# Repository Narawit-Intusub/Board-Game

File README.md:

# Modular Smart LED Matrix (กระดานไฟ LED อัจฉริยะต่อขยายได้อิสระสำหรับระบบเกมกระดาน)

---

## 1. ภาพรวมโปรเจกต์ (Project Overview)

**Modular Smart LED Matrix** คือ กระดานแสดงผลไฟ LED อัจฉริยะแบบต่อขยายได้อิสระ (Modular Interactive Tabletop Gaming Grid) ออกแบบมาเพื่อเป็นกระดานเล่นเกมแบบ Interactive ร่วมกับเอนจินเกม (เช่น Unity หรือ PC) และหน้าจอแสดงผลกราฟิกแบบปรับเปลี่ยนรูปทรงได้อย่างอิสระ

ระบบถูกออกแบบภายใต้สถาปัตยกรรม **Smart Tile (Distributed Grid Architecture)** โดยแต่ละแผ่นกระดานมีขนาด **$192.0 \times 192.0\text{ mm}$ ($19.2 \times 19.2\text{ cm}$)** แบ่งเป็น **16 ช่องตาราง ($4 \times 4$ Cells ช่องละ $48.0 \times 48.0\text{ mm}$)** แต่ละช่องมีไฟ 4 หลอด (รวม 64 หลอดต่อแผ่น) ขับแสดงผลเฉพาะในบอร์ดตัวเองอย่างอิสระ ไม่ต่อสายไฟ LED เป็นโซ่อนุกรมข้ามบอร์ด

```text
Unity / PC
    │
    │ USB DATA
    ▼
┌───────────────────────────────┐
│ MASTER                        │
│                               │
│ ESP32 Gateway                 │
│    │ Internal UART            │
│    ▼                          │
│ ATtiny1604 Tile Controller    │
│    ├── LED Matrix ของ Master  │
│    └── Magnetic Bus N/E/S     │
└───────────────┬───────────────┘
                │
        VBUS, TX, RX, GND
                │
       ┌────────┴────────┐
       ▼                 ▼
┌─────────────┐   ┌─────────────┐
│ Slave Tile  │   │ Slave Tile  │
│ ATtiny1604  │   │ ATtiny1604  │
└─────────────┘   └─────────────┘
```

---

## 2. โครงสร้างระบบ (System Structure)

ชุดต้นแบบประกอบด้วยกระดานทั้งหมด 4 แผ่น:

| บอร์ด | ตัวควบคุม | หน้าที่หลัก |
| :--- | :--- | :--- |
| **Master (1 แผ่น)** | **ESP32 Wemos D1 Mini + ATtiny1604** | • **ESP32:** เกตเวย์เชื่อม Unity ผ่าน USB, เก็บ Topology ทั้งระบบ, คำนวณ Global Grid, แยก Packet ตาม Tile ID, ตรวจสอบสถานะระบบ<br>• **ATtiny1604:** ควบคุม Tile ของ Master, ขับ 64 LEDs, จัดการ Magnetic Bus N/E/S |
| **Slave 1 (1 แผ่น)** | **ATtiny1604** | ขับ LED 64 ดวงในตัว, รับ-ส่งต่อ Packet, ตรวจจับเพื่อนบ้าน |
| **Slave 2 (1 แผ่น)** | **ATtiny1604** | ขับ LED 64 ดวงในตัว, รับ-ส่งต่อ Packet, ตรวจจับเพื่อนบ้าน |
| **Slave 3 (1 แผ่น)** | **ATtiny1604** | ขับ LED 64 ดวงในตัว, รับ-ส่งต่อ Packet, ตรวจจับเพื่อนบ้าน |

### สรุปรวมอุปกรณ์หลักของระบบ:
* **ESP32:** จำนวน 1 ตัว (อยู่บนบอร์ด Master เท่านั้น ทำหน้าที่ Gateway ระดับระบบ)
* **ATtiny1604:** จำนวน 4 ตัว (ประจำทุกแผ่น แผ่นละ 1 ตัว ทำหน้าที่ Tile Controller มาตรฐานเดียวกัน)
* **USB Data:** ต่อคอมพิวเตอร์เฉพาะบอร์ด Master เพียงจุดเดียว
* **Power Input:** จ่ายไฟเข้าที่บอร์ด Master เพียงจุดเดียว แล้วส่งผ่านบัส `VBUS` ไปยังแต่ละแผ่น

---

## 3. หน้าที่ของแต่ละตัวควบคุม

### 3.1 หน้าที่ของ ESP32 (System Gateway)
* ติดต่อกับ Unity ผ่านสาย USB เพียงเส้นเดียว
* รับสถานะเกม ข้อมูลสีพิกัด และคำสั่งเฟรมภาพ
* บันทึกและวิเคราะห์โครงสร้างแผนผังทั้งหมดของระบบ (System Topology)
* คำนวณตำแหน่งสัมพัทธ์และการหมุนของแต่ละ Tile รวมเป็น Global Grid ผืนเดียว
* แยกข้อมูล Packet ตาม Tile ID
* ตรวจสอบสถานะและรายงานความผิดปกติของระบบ
* **ส่ง Packet ทั้งหมดให้ ATtiny1604 ของ Master ผ่าน Internal UART**
* *ESP32 ไม่ต้องต่อเข้าหัวแม่เหล็กภายนอกโดยตรง และไม่ต้องขับ LED โดยตรง*

### 3.2 หน้าที่ของ ATtiny1604 (Tile Controller ประจำทุกแผ่น รวม 4 ตัว)
* มีรหัส **Tile ID** ประจำตัว
* ขับไฟ LED ภายในแผ่นตัวเอง (64 LEDs จากข้อมูลสี 16 ช่อง)
* จัดการหน่วยความจำสี 16 ช่อง (Active Buffer และ Back Buffer)
* รับและส่งต่อ Packet ข้อมูลตามเส้นทางเครือข่าย
* ส่งข้อความ `HELLO` เพื่อค้นหาเพื่อนบ้าน
* **ตรวจจับเพื่อนบ้านและทิศทางการเชื่อมต่อเมื่อได้รับข้อความ `HELLO` ทางขา RX แยกแต่ละทิศ (`LINK_RX_N/E/S/W`)**
* รอรับสัญญาณแสดงผลพร้อมกัน (`FRAME_COMMIT`)
* รายงานสถานะกลับไปยัง ESP32 ผ่านโครงข่ายบัส
* **ATtiny บน Master และ Slave ใช้ Firmware สถาปัตยกรรมพื้นฐานชุดเดียวกัน**

---

## 4. บัสแม่เหล็ก 4 จุด (4-Pin Magnetic Link)

แต่ละขอบที่เชื่อมต่อระหว่างบอร์ดมีพินสัญญาณ 4 พิน:

$$\text{[ VBUS ]} \quad \vert \quad \text{[ LINK_TX ]} \quad \vert \quad \text{[ LINK_RX ]} \quad \vert \quad \text{[ GND ]}$$

```text
  Female Connector (North / East)       Male Connector (South / West)
      +---------------------+               +---------------------+
      | (1)  (2)  (3)  (4)  |               | (1)  (2)  (3)  (4)  |
      | VBUS LinkTX LinkRX GND|             | GND LinkTX LinkRX VBUS|
      +---------------------+               +---------------------+
```

### 4.1 การจับคู่เมื่อประกบบอร์ด (Poka-Yoke 180° Inversion):
เมื่อนำขอบ Female ประกบกับขอบ Male หลังหมุน 180° พินจะจับคู่ตรงกันอย่างถูกต้อง:
* $\text{Pin 1 (VBUS)} \longleftrightarrow \text{Pin 4 (VBUS)}$: บัสไฟเลี้ยงหลัก
* $\text{Pin 2 (LINK_TX)} \longleftrightarrow \text{Pin 3 (LINK_RX)}$: สายส่งข้อมูลชนสายรับข้อมูล
* $\text{Pin 3 (LINK_RX)} \longleftrightarrow \text{Pin 2 (LINK_TX)}$: สายรับข้อมูลชนสายส่งข้อมูล
* $\text{Pin 4 (GND)} \longleftrightarrow \text{Pin 1 (GND)}$: ระนาบกราวด์ร่วม

### 4.2 ทิศทางขั้วต่อในแต่ละบอร์ด:
* **Master มี 3 ทิศ:** **North, East, South** (เว้นด้าน **West** ไว้สำหรับช่องรับไฟหลักและพอร์ต USB สื่อสารกับคอมพิวเตอร์)
* **Slave มีครบ 4 ทิศ:** **North, East, South, West**

### 4.3 สถาปัตยกรรมการรับ-ส่งสัญญาณ (Directional RX & Shared TX):
บนแต่ละ Tile:
* มีขา **LINK_RX แยกอิสระ 4 ทิศทาง:** `LINK_RX_N`, `LINK_RX_E`, `LINK_RX_S`, `LINK_RX_W` ทำให้ระบุทิศทางของแพ็กเก็ตที่ส่งเข้ามาได้อย่างแม่นยำ
* มีขา **LINK_TX หนึ่งเส้นใช้ร่วมกันทุกด้าน:** เมื่อ Tile สั่งส่งข้อมูล ข้อมูลจะบรอดคาสต์ออกไปยังเพื่อนบ้านทุกด้านพร้อมกัน

---

## 5. รูปแบบแพ็กเก็ตและการป้องกันข้อมูลวนซ้ำ (Packet Architecture & Loop Prevention)

เนื่องจากขา `LINK_TX` เป็นสายร่วมที่กระจายสัญญาณออกทุกด้านพร้อมกัน Packet จึงต้องมีโครงสร้างข้อมูลกำกับ:

```text
+-----------+----------------+-----------------+--------------+-----+-----+--------+
| Source ID | Destination ID | Sequence Number | Frame Number | TTL | CRC | Data.. |
+-----------+----------------+-----------------+--------------+-----+-----+--------+
```

* **Source ID / Destination ID:** ระบุโหนดต้นทางและปลายทาง (หรือ Broadcast ID)
* **Sequence Number:** ลำดับของแพ็กเก็ต
* **Frame Number:** เลขเฟรมภาพสำหรับการซิงก์แสดงผล
* **TTL (Time-To-Live):** ลดค่าลงทีละ 1 ทุกครั้งที่ส่งต่อ เพื่อตัดวงจรแพ็กเก็ตตกค้าง
* **CRC:** ตรวจสอบความถูกต้องของข้อมูล
* **การป้องกันข้อมูลวนซ้ำ (Deduplication):** แต่ละ Tile จะจดจำ Sequence Number ล่าสุด และ**ไม่ประมวลผลแพ็กเก็ตเดิมซ้ำ** ช่วยป้องกันปัญหาข้อมูลวนลูปในกรณีที่มีเส้นทางเชื่อมต่อหลายทาง

---

## 6. เส้นทางข้อมูลที่ถูกต้อง (Data Flow Pipeline)

```text
Unity
  └──► ESP32 (Master)
         └──► ATtiny1604 (Master)
                ├──► ขับไฟ LED 64 ดวงบน Master
                └──► Magnetic Link (LINK_TX)
                       └──► ATtiny1604 (Slave Tile)
                              ├──► ขับไฟ LED 64 ดวงบน Slave
                              └──► ส่งต่อไปยัง Slave ถัดไป
```

* **Master Tile:** Unity $\rightarrow$ ESP32 $\rightarrow$ ATtiny Master $\rightarrow$ LED Master
* **Slave Tiles:** Unity $\rightarrow$ ESP32 $\rightarrow$ ATtiny Master $\rightarrow$ Magnetic Link $\rightarrow$ ATtiny Slave $\rightarrow$ ส่งต่อไปยัง Slave ถัดไป
* **ESP32 ไม่ส่งข้าม ATtiny Master ไปยังบอร์ดลูกโดยตรง**

---

## 7. สถาปัตยกรรมระบบไฟ (Power Architecture)

หลักการจ่ายไฟของระบบกำหนดไว้ดังนี้:

```text
Power Input
   └──► Master Protection
          └──► VBUS (ส่งผ่านขั้วต่อแม่เหล็กไปยังทุกแผ่น)
                 └──► Local Power Converter ในแต่ละ Tile
                        └──► 5V คงที่สำหรับขับ LED และเลี้ยง ATtiny1604
```

> [!IMPORTANT]
> **ข้อกำหนดในการออกแบบภาคจ่ายไฟ:**
> 1. **ใช้ชื่อบัสกลางว่า `VBUS`:** ไม่ส่งตรง 5V ผ่านทุกบอร์ดในระยะยาว เพื่อรองรับการจ่ายแรงดันที่สูงขึ้น (เช่น 9V–12V) แล้วใช้ Local Step-Down Converter ลดเป็น 5V ภายในแต่ละแผ่น เพื่อลดแรงดันตกคร่อม (Voltage Drop) และลดกระแสบนพินแม่เหล็ก
> 2. **ยังไม่ล็อกเบอร์อุปกรณ์และแรงดัน VBUS ในสเปกหลัก:** รายละเอียดของแรงดัน VBUS, ชนิดคอนเนคเตอร์ไฟเข้า, ชนิดวงจรแปลงไฟ, อุปกรณ์วัดกระแส, และพิกัด TVS (ห้ามล็อก SMAJ5.0A หาก VBUS มีโอกาสสูงกว่า 5V) จะสรุปหลังจากการทดสอบพิกัดกระแสจริงของหัวแม่เหล็กและกำลังวัตต์สูงสุดของ LED ทั้งระบบ
> 3. **ตัวต้านทาน CC 5.1kΩ:** ทำหน้าที่ระบุสถานะ Sink บนพอร์ต USB Type-C พื้นฐานเท่านั้น ไม่ได้รับรองการจ่ายกระแส 5V/3A และไม่ใช่ระบบเจรจาแรงดัน USB-PD

---

## 8. การจัดการระดับแรงดันสัญญาณ (Logic Level Translation)

* **หาก ATtiny1604 เลี้ยงด้วยไฟ 5V:** สัญญาณ GPIO เอาต์พุต (รวมถึงขาขับ LED `LED_DATA`) จะมีระดับแรงดันเป็น 5V CMOS Logic อยู่แล้ว จึงสามารถขับขา DIN ของโมดูล WS2812B ได้โดยตรงโดยไม่ต้องใช้ Level Shifter 3.3V$\rightarrow$5V หน้า LED
* **จุดที่ต้องแปลงระดับแรงดัน (Level Shifting):** คือส่วนเชื่อมต่อระหว่าง **ESP32 (แรงดันสัญญาณ 3.3V)** กับ **ATtiny1604 (แรงดันสัญญาณ 5V)** บนบอร์ด Master เพื่อให้การส่งข้อมูล UART ภายในทำงานได้อย่างถูกต้องและปลอดภัย

---

## 9. เอกสารอ้างอิงเฉพาะบอร์ด (Detailed Documentation Links)

* 📖 **[เอกสารวงจรและฮาร์ดแวร์บอร์ดแม่ (Master Controller Board README)](hardware/master/README.md)**
* 📖 **[เอกสารวงจรและฮาร์ดแวร์บอร์ดลูก (Slave Expansion Board README)](hardware/slave/README.md)**

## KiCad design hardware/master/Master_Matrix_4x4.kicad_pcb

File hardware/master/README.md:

# Master Controller Board (บอร์ดแม่) - Dual-MCU Smart Tile (ESP32 + ATtiny1604)

เอกสารนี้อธิบายรายละเอียดการออกแบบทางฮาร์ดแวร์ บล็อกการทำงาน หน้าที่ของแต่ละโมดูล และโครงสร้างทางวิศวกรรมของ **Master Controller Board** (ไฟล์ KiCad: [Master_Matrix_4x4.kicad_sch](Master_Matrix_4x4.kicad_sch), [Master_Matrix_4x4.kicad_pcb](Master_Matrix_4x4.kicad_pcb)) ภายใต้สถาปัตยกรรม **Dual-MCU Smart Tile Grid**

---

## 1. ภาพรวมบอร์ดแม่ (Master Board Overview)

**Master Controller Board** ขนาดแผ่น **$192.0 \times 192.0\text{ mm}$ ($19.2 \times 19.2\text{ cm}$)** แบ่งเป็น **16 ช่องตาราง ($4 \times 4$ Cells ช่องละ $48.0 \times 48.0\text{ mm}$)** แต่ละช่องติดตั้งไฟ LED 4 ดวงแบบ $2 \times 2$ (รวม 64 หลอด) ทำหน้าที่เป็นทั้ง **พื้นที่เล่นในตัว** และ **เกตเวย์เชื่อมต่อกับคอมพิวเตอร์/Unity**

### สถาปัตยกรรมชิปคู่บนบอร์ดแม่ (Dual-MCU Architecture):
บอร์ดแม่รวมไมโครคอนโทรลเลอร์ 2 ตัวไว้บนแผ่นเดียว เพื่อแยกบทบาทหน้าที่อย่างชัดเจน:

1. **ESP32 Gateway (`U1`):**
   - เชื่อมต่อกับ Unity / PC ผ่านสาย USB ทางขอบด้านซ้าย (West)
   - รับข้อมูลเกม, สถานะ, ข้อมูลสี และค่าความสว่างจาก Unity
   - เก็บโครงสร้างแผนผังความสัมพันธ์ทั้งระบบ (System Topology Map)
   - คำนวณ Global Grid และแปลงพิกัดสากล
   - แยกข้อมูล Packet ตาม Tile ID
   - ตรวจสอบสถานะการทำงานของระบบ
   - **ส่งทุก Packet ให้ ATtiny1604 ของบอร์ดแม่ผ่าน Internal UART**
   - *ESP32 ไม่ต่อเข้าหัวแม่เหล็กภายนอกโดยตรง และไม่ขับ LED โดยตรง*

2. **ATtiny1604 Master Tile Controller (`U_ATTINY`):**
   - ทำหน้าที่เป็น Smart Tile ประจำบอร์ดแม่ โดยใช้ **Firmware สถาปัตยกรรมเดียวกับบอร์ดลูก**
   - รับ Packet ข้อมูลจาก ESP32
   - จัดการเก็บสี 16 ช่องในหน่วยความจำ (Active Buffer และ Back Buffer)
   - ขับไฟ LED 64 ดวงในบอร์ดตัวเอง (1 สี ขยายออกเป็น 4 หลอดต่อช่อง)
   - ขับสัญญาณออกสู่โครงข่ายแม่เหล็ก 3 ทิศทาง (**North, East, South**) ผ่านสาย `LINK_TX`
   - กระจายสัญญาณและส่งต่อแพ็กเก็ตไปยังบอร์ดลูก

```text
Unity Game Engine
       │ USB DATA
       ▼
+-------------------------------------------------------------------------+
|                        Master Controller Board                          |
|                                                                         |
|                     [ J_NORTH (Female Mag-4P) ]                         |
|                     (VBUS, Link TX, Link RX, GND)                       |
|                                  ^                                      |
|                                  |                                      |
|  [ POWER INPUT ]            +----+----+                                 |
|  [ USB TO UNITY ]           | ATtiny  | <---> [ J_EAST (Female) ]       |
|         │                   |  1604   |       (VBUS, TX, RX, GND)       |
|         ▼                   | Master  |                                 |
|   +-----------+  Internal   +----+----+                                 |
|   |   ESP32   |  UART            | DIN_LOCAL (5V Logic)                 |
|   |  Gateway  | ---------->      v                                      |
|   +-----------+ (Level Shift)+---------------+                          |
|         │                    |  LED Matrix   | (MOD1 -> MOD2 -> .. MOD16|
|  (System Mgmt)               |  (64 LEDs)    | (Local Driving Only)     |
|   (West Edge)                +---------------+                          |
|                                  |                                      |
|                                  v                                      |
|                     [ J_SOUTH (Male Mag-4P) ]                           |
|                     (VBUS, Link TX, Link RX, GND)                       |
+-------------------------------------------------------------------------+
```

---

## 2. ขั้วต่อแม่เหล็ก 3 ทิศทาง (3-Edge Magnetic Link Bus)

บอร์ด Master ติดตั้งขั้วต่อแม่เหล็กที่ขอบบอร์ด **3 ด้านเท่านั้น** ได้แก่ **North, East, South** (เว้นด้าน **West** ไว้สำหรับช่องรับไฟหลักและพอร์ต USB เชื่อมต่อคอมพิวเตอร์):

$$\text{Pin 1: [ VBUS ]} \quad \vert \quad \text{Pin 2: [ LINK_TX ]} \quad \vert \quad \text{Pin 3: [ LINK_RX ]} \quad \vert \quad \text{Pin 4: [ GND ]}$$

```text
  Female Connector (North / East)       Male Connector (South)
      +---------------------+               +---------------------+
      | (1)  (2)  (3)  (4)  |               | (1)  (2)  (3)  (4)  |
      | VBUS LinkTX LinkRX GND|             | GND LinkTX LinkRX VBUS|
      +---------------------+               +---------------------+
```

### การจับคู่สัญญาณเมื่อประกบกัน (Poka-Yoke 180° Inversion):
* **Pin 1 (VBUS) $\longleftrightarrow$ Pin 4 (VBUS):** บัสจ่ายไฟเลี้ยงหลักของโครงข่าย
* **Pin 2 (LINK_TX) $\longleftrightarrow$ Pin 3 (LINK_RX):** สายส่งข้อมูลชนสายรับข้อมูลของเพื่อนบ้าน
* **Pin 3 (LINK_RX) $\longleftrightarrow$ Pin 2 (LINK_TX):** สายรับข้อมูลชนสายส่งข้อมูลของเพื่อนบ้าน
* **Pin 4 (GND) $\longleftrightarrow$ Pin 1 (GND):** ระนาบกราวด์ร่วมของทั้งระบบ

---

## 3. เส้นทางข้อมูลและการกระจายสัญญาณ (Data Routing & Level Shifting)

1. **เส้นทางข้อมูล:**
   * Unity $\rightarrow$ ESP32 (ถอดรหัสและแยก Packet)
   * ESP32 $\rightarrow$ ATtiny Master (ผ่าน Internal UART)
   * ATtiny Master $\rightarrow$ ขับไฟ LED 64 ดวงบนบอร์ด Master
   * ATtiny Master $\rightarrow$ กระจายข้อมูลออกสู่ `LINK_TX` ขั้วต่อแม่เหล็ก N/E/S ไปยังบอร์ดลูก
2. **การแปลงระดับแรงดัน (Level Shifting):**
   * หาก ATtiny1604 ทำงานที่แรงดัน 5V เอาต์พุต GPIO ของ ATtiny จะเป็น 5V Logic อยู่แล้ว จึงขับขา DIN ของ WS2812B ได้โดยตรง
   * จุดที่ต้องแปลงระดับแรงดันคือระหว่าง **ESP32 (3.3V Logic)** กับ **ATtiny1604 (5V Logic)** บนสัญญาณ UART ภายใน เพื่อความเข้ากันได้ทางไฟฟ้าและความปลอดภัยของชิป
   * ทิศ ESP32 → ATtiny ใช้ `74AHCT1G125`; ทิศ ATtiny → ESP32 ใช้ตัวแบ่งแรงดัน 10kΩ/20kΩ เพื่อจำกัดสัญญาณประมาณ 3.3V
3. **Current monitor:** บัส I²C ของ INA219 มี pull-up 4.7kΩ ไปยัง `+3V3` แยกทั้ง SDA และ SCL

---

## 4. สถาปัตยกรรมระบบไฟ (Power Architecture)

หลักการจ่ายไฟของระบบ:
```text
Power Input
   └──► Master Protection
          └──► VBUS ผ่านขั้วต่อแม่เหล็ก
                 └──► Local Power Converter ในแต่ละ Tile
                        └──► 5V คงที่สำหรับขับ LED และเลี้ยง ATtiny1604
```

> [!NOTE]
> **การกำหนดสเปกภาคจ่ายไฟ:**
> * บัสส่งไฟระหว่างบอร์ดใช้ชื่อกลางว่า **`VBUS`** เพื่อรองรับการทดสอบแรงดันที่เหมาะสม (เช่น 5V ตรง หรือ 9V–12V ร่วมกับ Local Step-Down Converter) เพื่อลดปัญหากระแสสูงและแรงดันตกคร่อมบนพินแม่เหล็ก
> * สเปกของ Power Input, พิกัดแรงดัน VBUS, วงจรตรวจวัดกระแส, และเบอร์ไดโอด TVS จะถูกกำหนดอย่างเป็นทางการหลังทราบพิกัดกระแสจริงของหัวแม่เหล็กและกำลังวัตต์สูงสุดของ LED ทั้งระบบ (ไม่ล็อกเบอร์ SMAJ5.0A หาก VBUS ถูกปรับขึ้นสูงกว่า 5V)
> * ตัวต้านทาน CC 5.1kΩ บนพอร์ต Type-C ทำหน้าที่ระบุสถานะ Sink พื้นฐาน ไม่ได้รับรองการจ่าย 5V/3A และไม่ใช่ระบบ USB-PD
> * `R_BUS` เป็น **DNP โดยปริยาย** ห้ามประกอบเป็น 0Ω จนกว่าจะยืนยันว่าใช้ VBUS 5V แบบจำกัดกระแส หากต้องการขยายหลาย Tile ให้แทนตำแหน่งนี้ด้วย Local Power Converter ที่เลือกตามพิกัดจริง
> * ขา `VCC_(USB)` ของโมดูล ESP32 ไม่ผูกเข้ากับราง `+5V` ภายนอก เพื่อป้องกันการป้อนไฟย้อนเข้าสาย USB Data ของคอมพิวเตอร์

---

## 5. การส่งแพ็กเก็ตและตรวจจับเพื่อนบ้าน

* **การส่งข้อมูล (`LINK_TX`):** ATtiny Master ส่งออกทาง `LINK_TX` ซึ่งเชื่อมขนานไปยังขั้วต่อ N, E, S สัญญาณจะออกไปยังเพื่อนบ้านทุกด้านพร้อมกัน
* **การป้องกันข้อมูลวนซ้ำ (Deduplication):** Packet จะระบุ `Source ID`, `Destination ID`, `Sequence Number`, `Frame Number`, `TTL`, และ `CRC` ทุกโหนดจะไม่ประมวลผล Packet เดิมซ้ำ
* **การค้นหาเพื่อนบ้าน (Neighbor Discovery):** ขา `LINK_RX` แยกตามทิศทาง (`LINK_RX_N`, `LINK_RX_E`, `LINK_RX_S`) เมื่อได้รับข้อความ `HELLO` ทางขาใด จะทำให้ ATtiny ทราบทิศทางและบอร์ดที่เชื่อมต่ออยู่ทันที และส่งรายงานกลับไปยัง ESP32

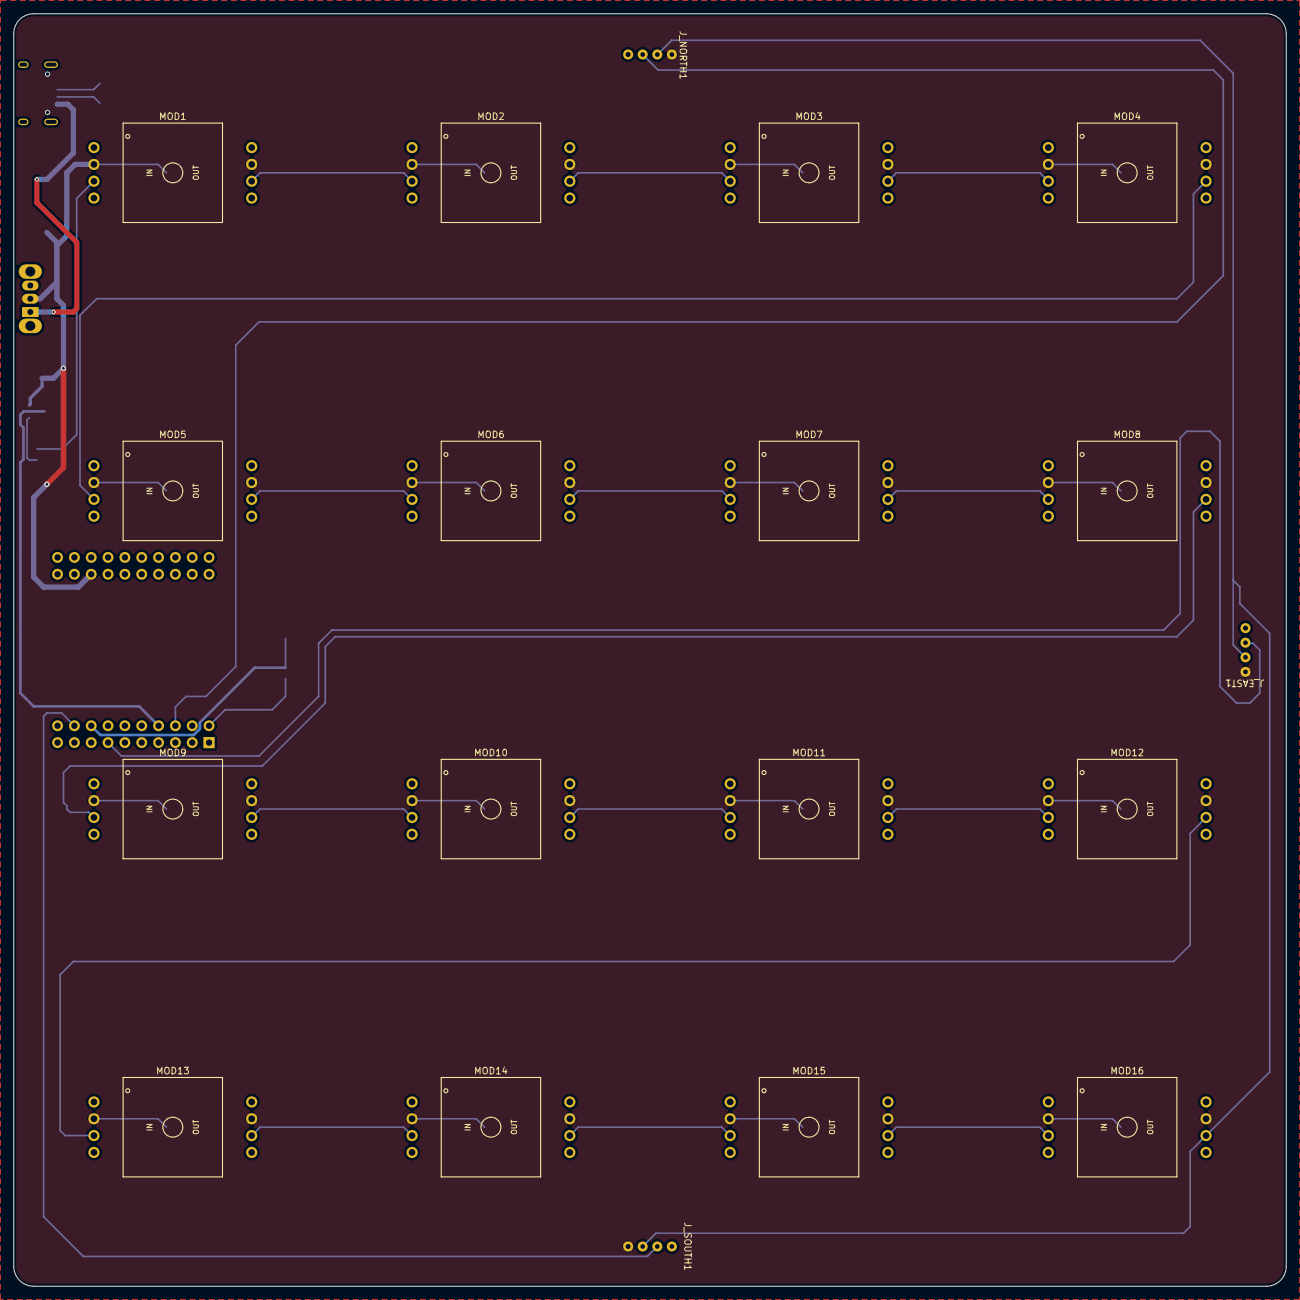
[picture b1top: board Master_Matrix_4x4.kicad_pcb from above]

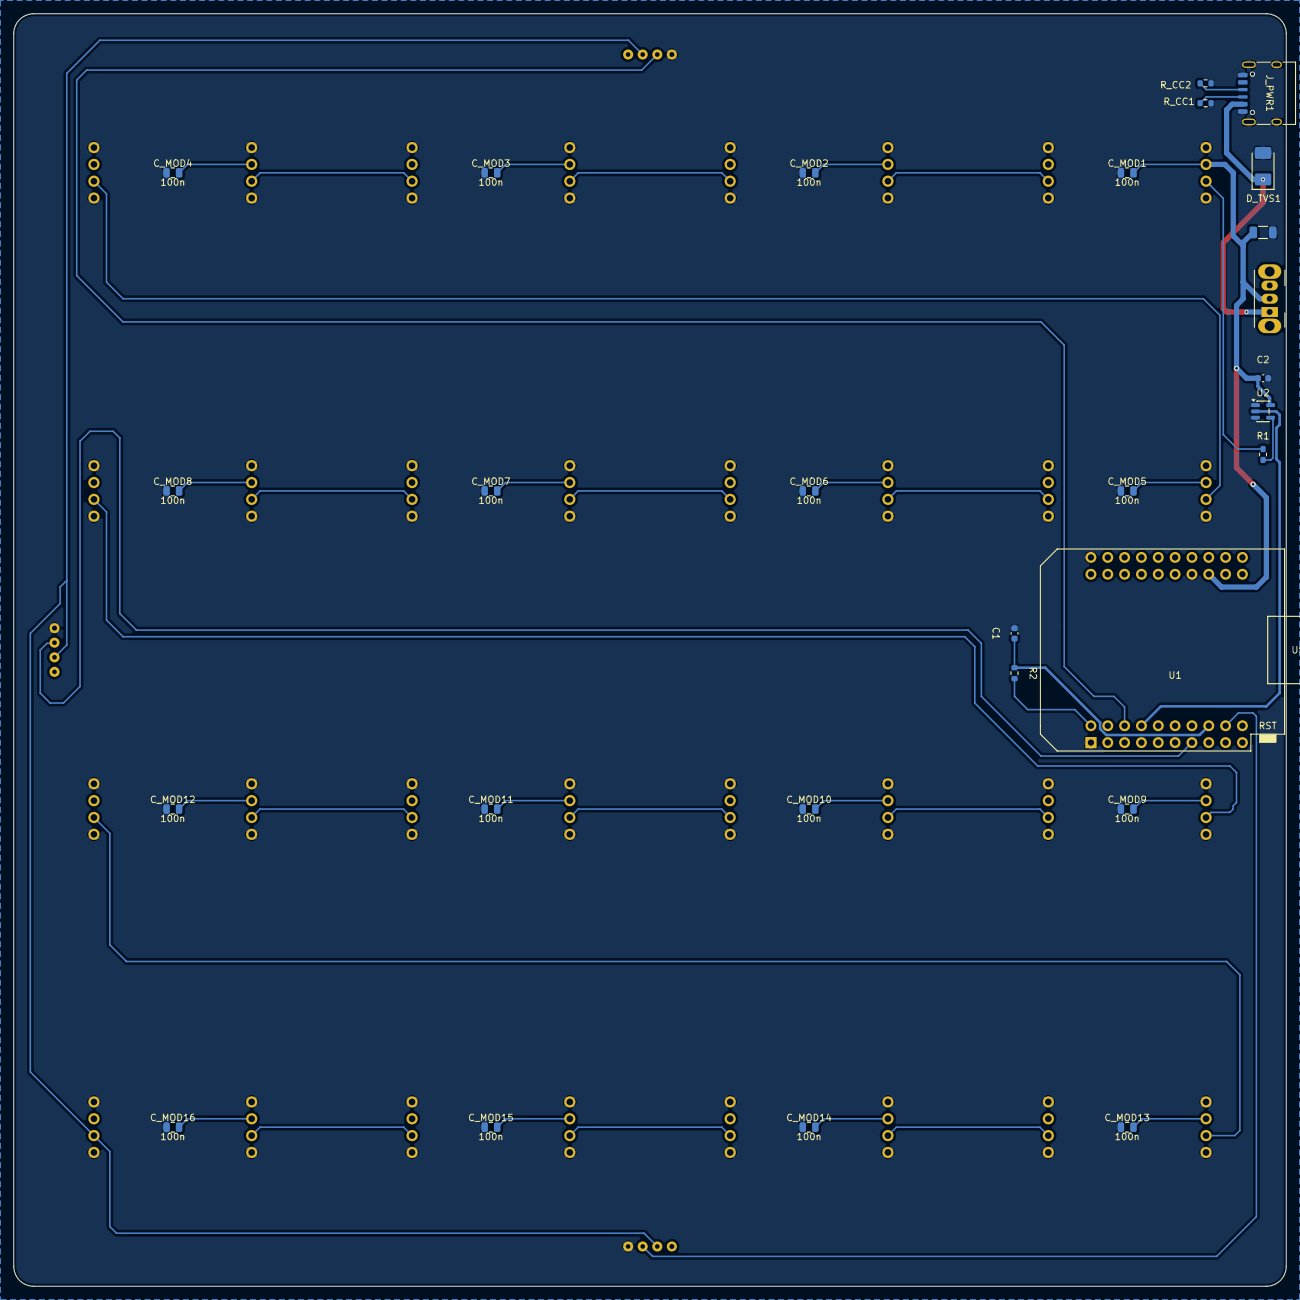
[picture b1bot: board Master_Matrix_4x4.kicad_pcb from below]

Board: 2 copper layers, 192.0 x 192.0 mm, 79 parts (28 on the bottom side), 29 nets.

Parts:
C1, C2: 100n; C_0603_1608Metric
C_BULK1: 100uF; C_1206_3216Metric
C_MOD1, C_MOD2, C_MOD3, C_MOD4, C_MOD5, C_MOD6, C_MOD7, C_MOD8, C_MOD9, C_MOD10, C_MOD11, C_MOD12, C_MOD13, C_MOD14, C_MOD15, C_MOD16: 100n; C_0805_2012Metric
D_TVS1: SMAJ5.0A; D_SMA
J_EAST1: Mag_East (Female); fakemag4pin90degFemale
J_IN1, J_IN2, J_IN3, J_IN4, J_IN5, J_IN6, J_IN7, J_IN8, J_IN9, J_IN10, J_IN11, J_IN12, J_IN13, J_IN14, J_IN15, J_IN16: PTH_4P_IN
J_NORTH1: Mag_North (Female); fakemag4pin90degFemale
J_OUT1, J_OUT2, J_OUT3, J_OUT4, J_OUT5, J_OUT6, J_OUT7, J_OUT8, J_OUT9, J_OUT10, J_OUT11, J_OUT12, J_OUT13, J_OUT14, J_OUT15, J_OUT16: PTH_4P_OUT
J_PWR1: USB_C_6P_3A_5V_IN; USB_C_Receptacle_6P_SMD
J_SOUTH1: Mag_South (Male); fakemag4pin90degMale
MOD1, MOD2, MOD3, MOD4, MOD5, MOD6, MOD7, MOD8, MOD9, MOD10, MOD11, MOD12, MOD13, MOD14, MOD15, MOD16: WS2812_Matrix_2x2; WS2812_Matrix_2x2_15x15mm
R1: 330R; R_0603_1608Metric
R2: 10k; R_0603_1608Metric
R_CC1, R_CC2: 5.1k; R_0603_1608Metric
SW1: SW_SPDT; SW_Slide_SPDT_Angled_CK_OS102011MA1Q
U1: esp32-wemos-d1-mini
U2: 74AHCT1G125; SOT-23-5

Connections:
+3V3: C1.1, R2.1, U1.16 (3V3)
+5V: C2.1, C_BULK1.1, C_MOD1.1, C_MOD2.1, C_MOD3.1, C_MOD4.1, C_MOD5.1, C_MOD6.1, C_MOD7.1, C_MOD8.1, C_MOD9.1, C_MOD10.1, C_MOD11.1, C_MOD12.1, C_MOD13.1, C_MOD14.1, C_MOD15.1, C_MOD16.1, J_EAST1.1 (VCC), J_IN1.2, J_IN2.2, J_IN3.2, J_IN4.2, J_IN5.2, J_IN6.2, J_IN7.2, J_IN8.2, J_IN9.2, J_IN10.2, J_IN11.2, J_IN12.2, J_IN13.2, J_IN14.2, J_IN15.2, J_IN16.2, J_NORTH1.1 (VCC), J_OUT1.2, J_OUT2.2, J_OUT3.2, J_OUT4.2, J_OUT5.2, J_OUT6.2, J_OUT7.2, J_OUT8.2, J_OUT9.2, J_OUT10.2, J_OUT11.2, J_OUT12.2, J_OUT13.2, J_OUT14.2, J_OUT15.2, J_OUT16.2, J_SOUTH1.1 (GND), SW1.2 (B), U1.35 (VCC_(USB)), U2.5 (VCC)
/DOUT4: J_IN5.3, J_OUT4.3
/DOUT8: J_IN9.3, J_OUT8.3
/DOUT12: J_IN13.3, J_OUT12.3
CC1: J_PWR1.3 (CC1), R_CC1.1
CC2: J_PWR1.4 (CC2), R_CC2.1
D01: J_NORTH1.3 (D1), U1.6 (IO_26/D0)
D11: J_EAST1.3 (D1), U1.13 (IO_14/TMS)
D21: J_SOUTH1.3 (D0), U1.18 (IO_13/TCK)
DIN: J_IN1.3, R1.2
DIN_3V3: U1.8 (IO_18/D5), U2.2 (A)
DOUT: J_EAST1.2 (D0), J_NORTH1.2 (D0), J_OUT16.3, J_SOUTH1.2 (D1)
GND: C1.2, C2.2, C_BULK1.2, C_MOD1.2, C_MOD2.2, C_MOD3.2, C_MOD4.2, C_MOD5.2, C_MOD6.2, C_MOD7.2, C_MOD8.2, C_MOD9.2, C_MOD10.2, C_MOD11.2, C_MOD12.2, C_MOD13.2, C_MOD14.2, C_MOD15.2, C_MOD16.2, D_TVS1.2 (A2), J_EAST1.4 (GND), J_IN1.1, J_IN1.4, J_IN2.1, J_IN2.4, J_IN3.1, J_IN3.4, J_IN4.1, J_IN4.4, J_IN5.1, J_IN5.4, J_IN6.1, J_IN6.4, J_IN7.1, J_IN7.4, J_IN8.1, J_IN8.4, J_IN9.1, J_IN9.4, J_IN10.1, J_IN10.4, J_IN11.1, J_IN11.4, J_IN12.1, J_IN12.4, J_IN13.1, J_IN13.4, J_IN14.1, J_IN14.4, J_IN15.1, J_IN15.4, J_IN16.1, J_IN16.4, J_NORTH1.4 (GND), J_OUT1.1, J_OUT1.4, J_OUT2.1, J_OUT2.4, J_OUT3.1, J_OUT3.4, J_OUT4.1, J_OUT4.4, J_OUT5.1, J_OUT5.4, J_OUT6.1, J_OUT6.4, J_OUT7.1, J_OUT7.4, J_OUT8.1, J_OUT8.4, J_OUT9.1, J_OUT9.4, J_OUT10.1, J_OUT10.4, J_OUT11.1, J_OUT11.4, J_OUT12.1, J_OUT12.4, J_OUT13.1, J_OUT13.4, J_OUT14.1, J_OUT14.4, J_OUT15.1, J_OUT15.4, J_OUT16.1, J_OUT16.4, J_PWR1.1 (GND), J_PWR1.6 (GND), J_PWR1.SH (SHIELD), J_SOUTH1.4 (VCC), R_CC1.2, R_CC2.2, U1.1 (GND), U1.22 (GND), U1.33 (GND), U2.1 (~OE), U2.3 (GND)
unnamed: J_IN2.3, J_OUT1.3
unnamed: J_IN3.3, J_OUT2.3
unnamed: J_IN4.3, J_OUT3.3
unnamed: J_IN6.3, J_OUT5.3
unnamed: J_IN7.3, J_OUT6.3
unnamed: J_IN8.3, J_OUT7.3
unnamed: J_IN10.3, J_OUT9.3
unnamed: J_IN11.3, J_OUT10.3
unnamed: J_IN12.3, J_OUT11.3
unnamed: J_IN14.3, J_OUT13.3
unnamed: J_IN15.3, J_OUT14.3
unnamed: J_IN16.3, J_OUT15.3
unnamed: R2.2, U1.2 (RST)
unnamed: R1.1, U2.4 (Y)
VBUS_IN: D_TVS1.1 (A1), J_PWR1.2 (VBUS), J_PWR1.5 (VBUS), SW1.1 (A)
